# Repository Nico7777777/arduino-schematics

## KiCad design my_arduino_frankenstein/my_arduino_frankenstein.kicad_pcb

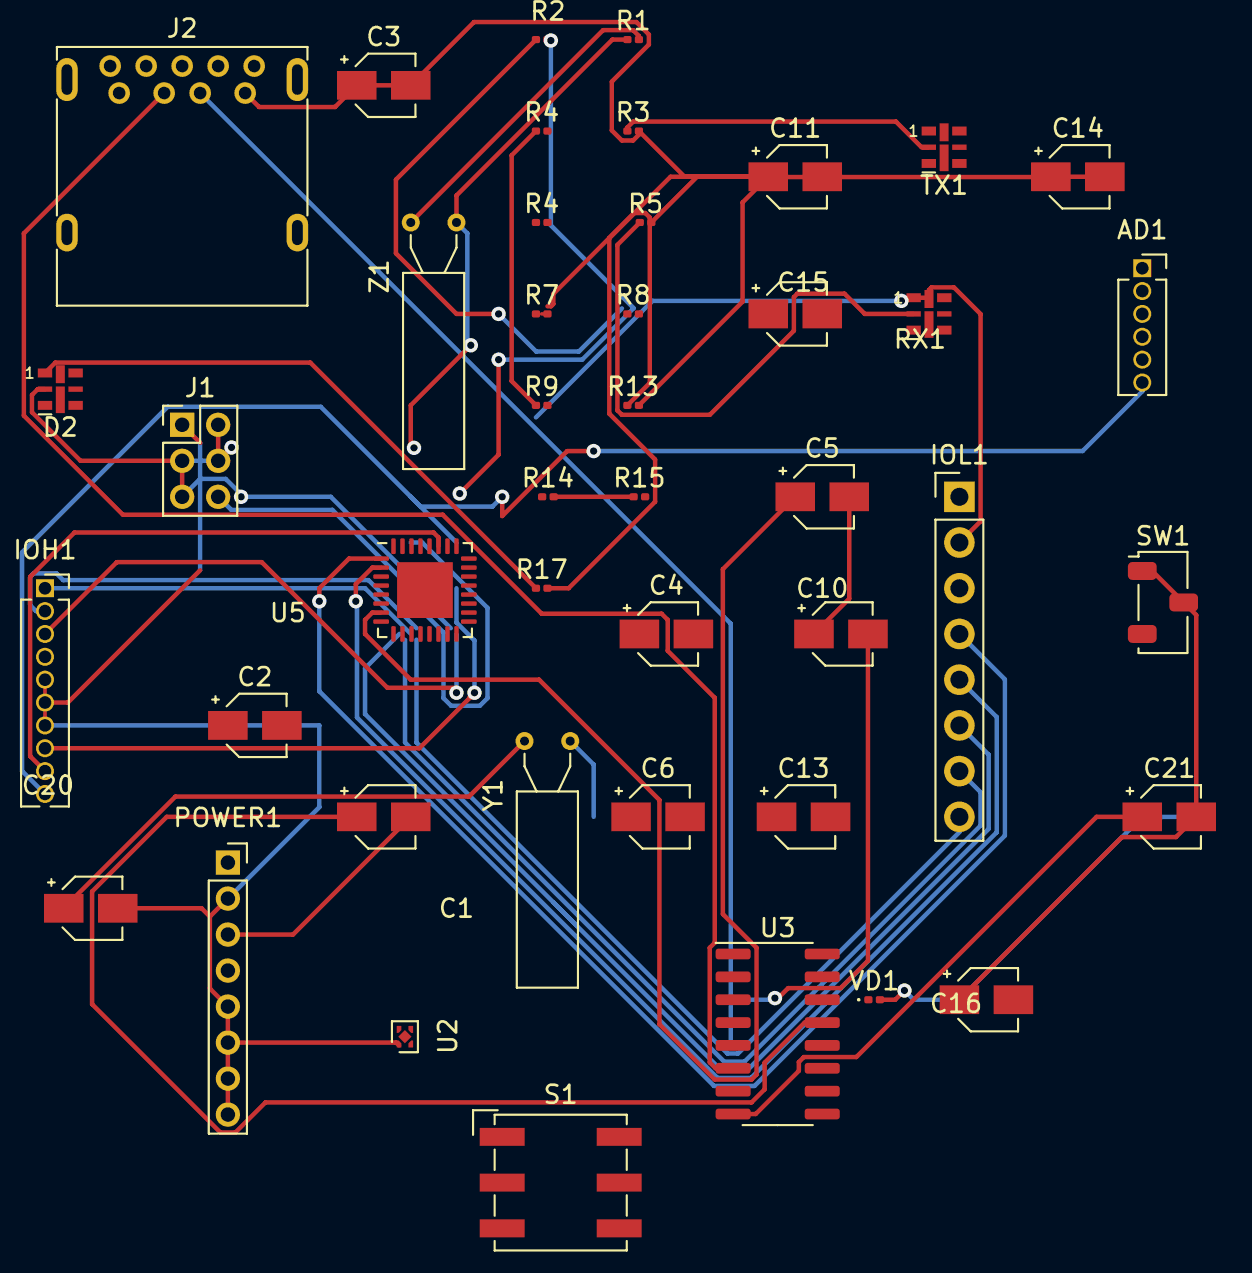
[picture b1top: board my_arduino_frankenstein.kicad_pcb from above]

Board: 2 copper layers, 44 parts (0 on the bottom side), 36 nets.

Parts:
AD1: 6X1F-H8,5; PinSocket_1x06_P1.27mm_Vertical
C1, C5, C6, C10: C; CP_Elec_3x5.3
C2: 47u 25V; CP_Elec_3x5.3
C3: 47u25v; CP_Elec_3x5.3
C4, C11, C13, C14, C15, C16: 100n; CP_Elec_3x5.3
C20, C21: 22p; CP_Elec_3x5.3
D2: ON; LED-APA102-2020
IOH1: 10X1F-H8,5; PinSocket_1x10_P1.27mm_Vertical
IOL1: 8X1F-H8,5; PinHeader_1x08_P2.54mm_Vertical
J1: Conn_02x03_Odd_Even; PinHeader_2x03_P2.00mm_Vertical
J2: USB3_A; USB3_A_Molex_48393-001
POWER1: 8X1F-H8,5; PinSocket_1x08_P2.00mm_Vertical
R1: 1M; R_0201_0603Metric
R2, R3, R4, R4#2, R5, R7, R8, R9, R17: 1k; R_0201_0603Metric
R13, R14, R15: 10k; R_0201_0603Metric
RX1: LED; LED-APA102-2020
S1: RESET; Nidec_Copal_SH-7010A
SW1: SW_DIP_x01; Nidec_Copal_CAS-120A
TX1: LED; LED-APA102-2020
U2: NCP115AMX250TCG; OnSemi_XDFN4-1EP_1.0x1.0mm_EP0.52x0.52mm
U3: CH340G; SOIC-16_3.9x9.9mm_P1.27mm
U5: ATmega328P-M; QFN-32-1EP_5x5mm_P0.5mm_EP3.1x3.1mm
VD1: D; LED_0201_0603Metric
Y1: 12Mhz; Crystal_AT310_D3.0mm_L10.0mm_Horizontal
Z1: 16Mhz; Crystal_AT310_D3.0mm_L10.0mm_Horizontal

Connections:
+5V: C2.1, C2.2, C3.1, C3.2, C4.1, C4.2, C5.2, C6.2, C10.1, C11.1, C11.2, C13.1, C14.1, C14.2, C16.1, C20.2, C21.2, IOH1.4, IOH1.5, IOH1.7, J1.6, J2.4 (GND), POWER1.2, POWER1.5, POWER1.6, POWER1.7, POWER1.8, R3.2, R5.2, R7.2, R13.1, R13.2, R17.2, SW1.1, SW1.2, U2.1 (OUT), U2.2 (GND), U2.3 (EN), U2.4 (IN), U2.5 (GND), U3.1 (GND), U3.16 (VCC), U5.3 (GND), U5.4 (VCC), U5.5 (GND), U5.6 (VCC), U5.15 (PB3), U5.16 (PB4), U5.18 (AVCC), U5.21 (GND), U5.33 (GND), VD1.1 (K)
GND: C13.2, C15.2, R15.2
unnamed: AD1.1, U5.23 (PC0)
unnamed: AD1.2, U5.24 (PC1)
unnamed: AD1.3, U5.25 (PC2)
unnamed: AD1.4, U5.26 (PC3)
unnamed: AD1.5, IOH1.9, U5.27 (PC4)
unnamed: AD1.6, IOH1.10, U5.28 (PC5)
unnamed: D2.1 (K), R17.1
unnamed: IOH1.1, U5.12 (PB0)
unnamed: IOH1.2, U5.13 (PB1)
unnamed: IOH1.3, U5.14 (PB2)
unnamed: D2.2 (A), IOH1.6, J1.1, J1.2, J1.3, J1.4, J1.5, U5.17 (PB5)
unnamed: C16.2, IOH1.8, U5.20 (AREF)
unnamed: IOL1.1, R2.2, R8.2, TX1.1 (K), U5.30 (PD0)
unnamed: IOL1.2, R4#2.2, R9.2, RX1.1 (K), U5.31 (PD1)
unnamed: IOL1.3, U5.32 (PD2)
unnamed: IOL1.4, U5.1 (PD3)
unnamed: IOL1.5, U5.2 (PD4)
unnamed: IOL1.6, U5.9 (PD5)
unnamed: IOL1.7, U5.10 (PD6)
unnamed: IOL1.8, U5.11 (PD7)
unnamed: J2.3 (D+), U3.5 (UD+)
unnamed: J2.2 (D-), U3.6 (UD-)
unnamed: C1.2, POWER1.3, U5.29 (~RESET/PC6)
unnamed: R5.1, RX1.2 (A)
unnamed: R3.1, R7.1, TX1.2 (A)
unnamed: R4#2.1, R9.1, U3.3 (RXD)
unnamed: R2.1, R8.1, U3.2 (TXD)
unnamed: C10.2, U3.4 (V3)
unnamed: C20.1, U3.7 (XI), Y1.1
unnamed: C21.1, U3.8 (XO), Y1.2
unnamed: C1.1, U3.13 (~DTR)
unnamed: R14.2, R15.1
unnamed: C5.1, R1.1, U5.7 (XTAL1/PB6), Z1.2
unnamed: C6.1, R1.2, U5.8 (XTAL2/PB7), Z1.1

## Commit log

2023-10-17 init project
2023-10-17 progress 1
2023-10-18 progress 2
2023-10-18 progress 3
2023-10-21 progress 4
2023-10-24 progress 5
2023-10-25 progress 6
2023-10-29 final schematics for compact board
